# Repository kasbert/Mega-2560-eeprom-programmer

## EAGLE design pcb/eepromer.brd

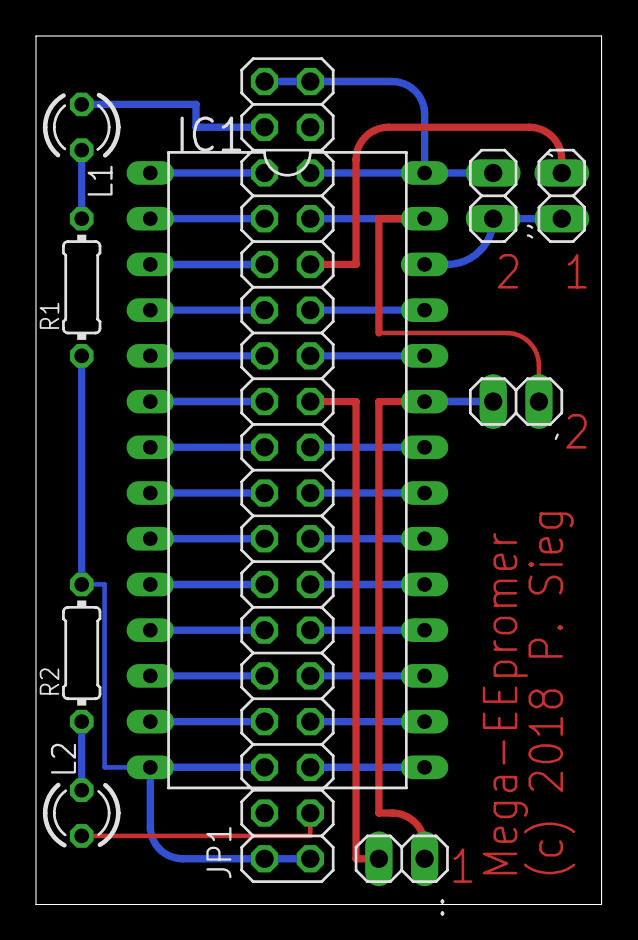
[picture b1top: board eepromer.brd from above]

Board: 2 copper layers, 31.4 x 48.2 mm, 10 parts (0 on the bottom side), 34 nets.

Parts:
': 1X02
,: 1X02
,,: 1X02
:: 1X02
IC1: DIL28-6
JP1: 2X18
L1, L2: LED3MM
R1, R2: 560; 0204/7

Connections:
S$1: ,.1, IC1.28, JP1.31, JP1.36
S$2: IC1.14, JP1.1, JP1.6, R1.1, R2.2
S$3: JP1.3, L2.A
S$4: ,,.2, JP1.27
S$5: ,.2, ,,.1, IC1.26
S$6: L2.K, R2.1
S$7: '.1, IC1.27, JP1.29
S$8: IC1.25, JP1.25
S$9: IC1.24, JP1.23
S$10: IC1.22, JP1.19
S$11: IC1.21, JP1.17
S$12: IC1.20, JP1.15
S$13: IC1.19, JP1.13
S$14: IC1.18, JP1.11
S$15: IC1.17, JP1.9
S$16: IC1.16, JP1.7
S$17: IC1.15, JP1.5
S$18: IC1.13, JP1.8
S$19: IC1.12, JP1.10
S$20: IC1.11, JP1.12
S$21: IC1.10, JP1.14
S$22: IC1.9, JP1.16
S$23: IC1.8, JP1.18
S$24: IC1.7, JP1.20
S$25: IC1.6, JP1.22
S$26: IC1.5, JP1.24
S$27: IC1.4, JP1.26
S$28: IC1.3, JP1.28
S$29: IC1.2, JP1.30
S$30: IC1.1, JP1.32
S$31: :.2, JP1.21
S$32: '.2, :.1, IC1.23
S$33: L1.K, R1.2
S$34: JP1.34, L1.A

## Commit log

2018-10-06 Add files via upload
    eeprommer.py - included command -P = enable software write protection + -U disable software write protection
    eeprom.ino - corrected SDP adresses
2018-10-08 Add files via upload
    Implemented -d (5) and -D (500) WriteDelay. 28C16 needs 500, other don't work with 500, they need 5.
2018-10-09 Add files via upload
    support chip selection by A=28C16, B=28C64 and C=28C256. SDP adresses and writedeleay will be set accordingly.
2020-01-25 remove old version
2020-01-25 Add read polling after write
2020-01-25 Use argparser
2020-01-25 Move files around
2020-01-25 Add hardware variant

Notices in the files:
pcb/eepromer.brd:
(c) 2018 P. Sieg
